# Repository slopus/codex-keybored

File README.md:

<h1 align="center">CODEX KEYBORED</h1>
<h3 align="center">WORK LOAFER EDITION · MECHANICS REV B · ELECTRONICS REV A2</h3>

<p align="center">
  A from-scratch, manufacturable parody of the Codex Micro: Fusion 360 mechanics,<br>
  four quoted CNC parts, a wired six-layer PCB, turnkey assembly instructions, and working USB HID firmware.
</p>

<p align="center">
  <a href="https://happy.engineering/codex-keybored/"><b>VIEW THE MANUFACTURING DOSSIER</b></a>
  &nbsp;·&nbsp;
  <a href="output/CODEX_KEYBORED_RevB_order_handoff.zip"><b>DOWNLOAD COMPLETE HANDOFF</b></a>
  &nbsp;·&nbsp;
  <a href="fusion/Codex_Micro_RevA.f3d"><b>OPEN FUSION ARCHIVE</b></a>
</p>

---

<h1 align="center">THIS IS NOT A DISCLAIMER.<br>THIS IS THE WHOLE POINT.</h1>

<h1 align="center">ABSOLUTELY EVERYTHING HERE IS 100% VIBE-CODED.</h1>

<h1 align="center">
  FROM THE FIRST PROMPT TO FUSION 360, KICAD, GERBERS, FIRMWARE,<br>
  AND A REAL UPLOAD INTO JLCPCB + JLCCNC.
</h1>

<h2 align="center">
  THIS IS THE PRODUCT STORY: ONE CONTINUOUS VIBE<br>
  FROM A PUBLIC PRODUCT IMAGE<br>
  TO A REAL, QUOTED, FACTORY-READY HARDWARE STACK.
</h2>

<p align="center">
  <b>THE DELIGHTFUL PART IS THAT THE VIBE DID NOT STOP WHEN THE WORK BECAME PHYSICAL.</b><br>
  It crossed industrial design, parametric CAD, CNC drawings, multilayer electronics, component sourcing,
  USB firmware, factory testing, pricing, and vendor handoff. Every layer is editable, inspectable, and ready to continue.
</p>

## One vibe, all the way to the factory

Most vibe-coded projects end at a screenshot. This one kept going until the pixels became toleranced solids, the solids became quoted CNC parts, the control layout became a routed six-layer PCB, the PCB became Gerbers/BOM/CPL, the firmware became checksummed factory binaries, and the whole stack became live JLC manufacturing jobs.

That is the fun of this repository: the same conversational build loop moves through every engineering discipline without hiding the seams. “The aluminum base is slightly tilted” became a **5° Fusion body**. “Not a foot, a ring” became a purchased **JIS G‑65 O-ring**, a concentric retention groove, refreshed STEP/DXF/PDF exports, a successful JLCCNC import, a **$68.31** live base quote, and a cleaned cart. “I do not want to solder switches” became a both-side PCBA configuration, consigned-parts manifest, 74-position placement file, manual assembly contract, flashing procedure, and functional acceptance test.

| Vibe-coding pass | What was created | Where it became real |
|---|---|---|
| **Look closely** | Public renders were compared, scaled, and converted into an explicit confirmed/measured/inferred datum set | Research notes + manufacturing dossier |
| **Make it solid** | A parametric 108 × 108 mm assembly, corrected wedge, captured light pipe, joystick cap, and purchased continuous grip ring | Fusion 360 scripts + four STEP/DXF packages + G‑65 vendor reference |
| **Make it electronic** | A clean-room STM32F072 architecture, matrix, USB-C, touch, joystick, 24 RGB pixels, six copper layers | KiCad source + 0-error DRC + IPC netlist |
| **Make it behave** | USB HID firmware, neutral F13–F24 map, RGB safety limit, factory browser test | BIN/HEX/ELF + SHA-256 checksums |
| **Make it buildable** | LCSC mappings, BOM/CPL, specialty-parts sourcing, manual operations, inspection gates | Turnkey factory ZIP + controlled SOP |
| **Make the factory answer** | CAD and fabrication files were uploaded into authenticated quote flows | Four current JLCCNC items + JLCMC G‑65 ring + JLCPCB job Y5 |

```text
PROMPT → RESEARCH → DIMENSIONS → FUSION 360 → STEP/DXF → JLCCNC
                     ↓
              ELECTRICAL PLAN → KICAD → GERBER/BOM/CPL → JLCPCB
                     ↓
              FIRMWARE → FACTORY TEST → TURNKEY HANDOFF → A FEW FINAL SCREWS
```

The result is not “AI made a picture of a keyboard.” The result is a versioned hardware project in which a vibe-driven decision can be traced from sentence to parameter, from parameter to geometry or net, and from production file to a factory price. **That end-to-end continuity is the project.**

---

## The whole device, not just a render

| Mechanical | Electronics | Factory route |
|---|---|---|
| **108 × 108 mm** outer envelope | **90 × 90 mm**, six copper layers | **4 CNC parts** already quoted |
| **5°** machined aluminum wedge | STM32F072 + USB-C + TinyUSB | **5 PCBs / 2 PCBA** in turnkey job Y5 |
| Parametric Fusion assembly + STEP/DXF | 12 keys + encoder + touch + joystick | Specialty parts consigned to the factory |
| Black POM, clear PMMA, 6061-T6, NBR | 24 reverse-mount RGB pixels | Flash, functional test, and evidence in SOP |
| Controlled drawing pack | **0 DRC violations / 0 unconnected nets** | Customer closes only a few enclosure screws |

<table>
  <tr>
    <td width="50%"><br><sub><b>FUSION 360 / TOP</b> — measured mechanical interface</sub></td>
    <td width="50%"><br><sub><b>FUSION 360 / SIDE</b> — corrected 5° wedge</sub></td>
  </tr>
  <tr>
    <td width="50%"><br><sub><b>PCB / TOP</b> — WORK LOAFER EDITION silk</sub></td>
    <td width="50%"><br><sub><b>PCB / BOTTOM</b> — controller island, power, matrix, RGB</sub></td>
  </tr>
</table>

## Yes: the factory does the hand work

> **ZERO SOLDERING AT HOME.** The production route asks JLC to place both-side SMD, manually install the twelve switches and encoder, fit the joystick/FFC, flash the STM32, exercise all 20 USB HID events, inspect all 24 RGB emitters, and install the caps on the primary unit. The customer-facing operation is enclosure closure after first-article approval.

The automatic JLC matcher uses the catalog-only [BOM](electronics/production/codex_micro_wired_revA_jlc_bom.csv) and [CPL](electronics/production/codex_micro_wired_revA_jlc_cpl.csv). The complete manual/secondary-operation contract is in the [turnkey SOP](electronics/production/CODEX_KEYBORED_RevA2_TURNKEY_SOP.md), [expanded BOM](electronics/production/codex_micro_wired_revA_turnkey_bom.csv), [74-position CPL](electronics/production/codex_micro_wired_revA_turnkey_cpl.csv), and [consigned-parts manifest](electronics/production/codex_micro_wired_revA_consigned_parts.csv).

```text
SOURCE SPECIALTY PARTS  →  BOTH-SIDE PCBA  →  MANUAL CONTROLS
         →  FLASH + FUNCTION TEST  →  PHOTO EVIDENCE  →  ENCLOSURE CLOSURE
```

## Live manufacturing snapshot

Quotes were captured in an authenticated JLC session on **July 17, 2026**. Prices are dynamic and exclude possible tax, duty, and engineering-review additions.

| Job | Configuration | Captured price |
|---|---|---:|
| CM2-001 upper housing | CNC polished black POM, qty 1 | **$88.97** |
| CM2-002 angled weight | CNC 6061-T6, 5° wedge + G‑65 groove, qty 1 | **$68.31** |
| CM2-003 light pipe | CNC clear cast PMMA, polished edges + frosted face, qty 1 | **$45.70** |
| CM2-004 joystick cap | CNC POM fit prototype, qty 1 | **$19.42** |
| CM2-005 continuous grip ring | JLCMC AMFG-P5-A65-65 / black NBR 65A, qty 1 | **$0.16** |
| **Mechanical subtotal** | Four current CNC parts + purchased ring | **$222.56** |
| **JLCPCB turnkey base** | Five PCBs + two both-side Standard PCBA | **$193.01** |
| **Captured manufacturing floor** | Mechanical merchandise + PCBA base, before manual review, special parts, tax/duty/shipping | **$415.57** |

The **$193.01** PCB/PCBA figure is a captured base, not a promise of a finished-device total. Programming, functional test, secondary manual operations, and consigned-part handling remain quote-after-review. The saved cart proves that the geometry and six-layer board can enter the vendor workflow; JLC engineering approval is still the gate before payment.

## What is actually in the repository

| Area | Source of truth | Ready-to-send artifact |
|---|---|---|
| Fusion mechanics | [`fusion/build_codex_micro_mechanical.py`](fusion/build_codex_micro_mechanical.py) | [`Codex_Micro_RevA.f3d`](fusion/Codex_Micro_RevA.f3d) |
| CNC geometry | Fusion BRep bodies | [`cnc/STEP/`](cnc/STEP/) + [`cnc/DXF/`](cnc/DXF/) |
| CNC dimensions | Parametric model + controlled notes | [`CM2_CNC_Drawing_Pack_RevB.pdf`](cnc/drawings/CM2_CNC_Drawing_Pack_RevB.pdf) |
| PCB connectivity/layout | [`codex_micro_wired_revA.kicad_pcb`](electronics/kicad/codex_micro_wired_revA.kicad_pcb) | [Gerber/drill ZIP](electronics/production/codex_micro_wired_revA_gerbers.zip) |
| Assembly data | Board-derived generator | [JLC BOM](electronics/production/codex_micro_wired_revA_jlc_bom.csv) + [JLC CPL](electronics/production/codex_micro_wired_revA_jlc_cpl.csv) |
| Principle schematic | Final routed connectivity | [Three-sheet PDF](output/pdf/CODEX_KEYBORED_RevA2_schematic.pdf) + [IPC-D-356](electronics/production/netlist/CODEX_KEYBORED_RevA2.ipc) |
| Firmware | [`firmware/stm32/`](firmware/stm32/) | [BIN](firmware/stm32/release/codeks_keybored_revA.bin) + [HEX](firmware/stm32/release/codeks_keybored_revA.hex) + [checksums](firmware/stm32/release/SHA256SUMS.txt) |
| Factory contract | Mechanics Rev B + electronics Rev A2 | [Complete order handoff ZIP](output/CODEX_KEYBORED_RevB_order_handoff.zip) + [mechanical factory ZIP](output/CODEX_KEYBORED_RevB_mechanical_factory_handoff.zip) |
| Full report | Evidence, screenshots, prices, sources | [Single-page dossier](https://happy.engineering/codex-keybored/) + [Rev B PDF](output/pdf/CODEX-KEYBORED-Manufacturing-Dossier-RevB.pdf) |

## Electrical architecture

- STM32F072CBT6, 128 KB flash, crystal-less HSI48 + CRS USB.
- USB-C device input, dual 5.1 kΩ CC resistors, USBLC6 ESD protection.
- Six layers: `F.Cu`, GND plane, two signal layers, `+5V` plane, `B.Cu`.
- Twelve low-profile matrix switches plus clickable encoder.
- Capacitive touch and two-channel analog planar joystick.
- 24 × SK6812MINI-E: twelve per-key, nine underglow, three status.
- Build-verified TinyUSB firmware with BIN/HEX/ELF artifacts and a browser factory test.
- Housing interface intentionally remains compatible with a future replacement ESP32-S3/BLE board.

## Mechanical datum set

The coordinate origin is the device center. `+Y` points toward the rear edge; `+Z` points upward.

| Parameter | Value | Confidence | Basis |
|---|---:|---|---|
| Key pitch | 19.05 mm | **CONFIRMED** | Work Louder MX keycap specification |
| Installed keyboard switches | 12 | **CONFIRMED** | Visible layout + Creator Micro 2 specification |
| Total mechanical switch inputs | 13 | **CONFIRMED** | Includes encoder push |
| Outer envelope | 108 × 108 mm | **MEASURED** | Official top render scaled from key centers |
| Top PCB/panel | 90 × 90 × 1.6 mm | **MEASURED / INFERRED** | Render scale + standard PCB thickness |
| PCB screw pitch | 78 × 78 mm | **MEASURED** | Provisional ±0.5 mm |
| Upper housing | 108 × 108 × 10.3 mm, R14 | **MEASURED** | Public front/side/top renders |
| Aluminum bottom | Ø94 mm, 3.8→12.0 mm, 5° | **MEASURED / INFERRED** | Side profile + CNC construction |
| G‑65 retention groove | Ø67.5 mm centerline × 3.6 W × 2.2 D | **ENGINEERED** | G‑65 section, screw clearance, 1.6 mm minimum Al floor |
| Continuous grip ring | JIS B 2401 G‑65, ID 64.4, section 3.1, OD 70.6 mm | **PURCHASED / VERIFIED** | JLCMC AMFG-P5-A65-65 |
| Joystick candidate | Alps RKJXY1000006 | **CANDIDATE** | Available electrical/mechanical sibling |

Confidence language is deliberate:

- **CONFIRMED** — explicitly published by OpenAI, Work Louder, or a component manufacturer.
- **MEASURED** — scaled from a public, near-orthographic product render.
- **INFERRED** — a manufacturable placeholder that still requires physical first-article inspection.
- **ENGINEERED** — a derived interface sized from known parts, tolerances, and adjacent clearances.
- **PURCHASED / VERIFIED** — an exact orderable catalog part with checked dimensions and a live cart entry.

## CNC material directions

The current quoted Rev B build uses polished black POM for the upper housing and joystick cap, black-anodized 6061-T6 for the 5° base, clear cast PMMA for the captured light pipe, and a purchased black NBR G‑65 ring. A wood upper remains a future material experiment, but it is not the current cart configuration.

All four STEP files passed JLC's automated CNC import. The current bottom was explicitly corrected from an early flat disc to the observed **5° wedge**, then revised again with the G‑65 retention groove before the **$68.31** configuration was saved. Obsolete flat/no-groove parts and individual rubber feet were removed from the cart.

## Reproduce it

1. Open or create the Fusion document named `Codex`, then run [`fusion/build_codex_micro_mechanical.py`](fusion/build_codex_micro_mechanical.py).
2. Export/audit CNC bodies with the scripts in [`fusion/`](fusion/) and compare them with the controlled drawing pack.
3. Open the board in KiCad 10 and verify the committed DRC report before regenerating fabrication data.
4. Build the STM32 target from [`firmware/stm32/`](firmware/stm32/) or use the checksummed release image.
5. Upload the Gerber ZIP, JLC BOM/CPL, CNC STEP files, drawing pack, and turnkey factory ZIP.
6. Do not authorize production until JLC DFM, polarity/rotation, manual-operation scope, and first-article dimensions are reviewed.

## Prototype status and provenance

This is an **independent private prototype**, reconstructed from official public product renders and published platform/component documentation. It is not an official OpenAI or Work Louder CAD/electronics release, is not affiliated with or endorsed by either company, and contains no leaked manufacturing data.

The digital production gate is clean: Gerbers, drill files, BOM/CPL, IPC netlist, three-sheet principle schematic, firmware, STEP/DXF, drawings, and vendor quote evidence are present. The physical gate is still open: no fabricated Rev A2 board has completed electrical bring-up, EMC evaluation, or dimensional fit-check. Use a current-limited supply, verify the 3.3 V rail and SWD first, and treat the first order as an engineering prototype.

Primary research links and detailed source notes live in the [manufacturing dossier](https://happy.engineering/codex-keybored/) and [`firmware-and-compliance-notes.md`](firmware-and-compliance-notes.md).

---

<h2 align="center">PRESS KEYS. SHIP BUGS.</h2>
<p align="center"><b>CODEX KEYBORED / WORK LOAFER EDITION / MECHANICS REV B + ELECTRONICS REV A2</b></p>

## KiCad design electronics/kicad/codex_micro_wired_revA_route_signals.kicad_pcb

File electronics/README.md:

# CODEX KEYBORED Wired Rev A2 — production notes

This directory contains a mechanically compatible **wired prototype**, not a
reverse-engineered copy of the unpublished Work Louder electronics.  The board
uses a clean-room STM32F072/USB-C design and keeps the 90 × 90 mm top-panel outline
so a later ESP32-S3/BLE controller can replace it without changing the housing.

## Electrical architecture

- Six copper layers: `F.Cu`, ground plane, two signal layers, `+5V` plane,
  `B.Cu`.
- STM32F072CBT6 with 128 KB internal flash, HSI48 + CRS crystal-less USB, and
  ME6211 3.3 V LDO. No external flash or crystal is required.
- USB-C device input with two 5.1 kΩ CC resistors and USBLC6 ESD protection.
  The reversible connector pairs cross on `SIGNAL_1` / `SIGNAL_2` before PA11/PA12.
- Twelve Gateron KS-33 / wrk. LP1-family matrix switches plus encoder push.
- Clickable encoder, TTP223-class touch input and two-channel analog joystick.
- 24 SK6812MINI-E pixels through a 5 V-compatible AHCT buffer: 12 per-key,
  nine perimeter underglow and three status LEDs.
- NRST, BOOT0 and SWD bring-up access.

The PCB is generated from `generate_wired_reva.py`; it deliberately does not
depend on a GUI schematic editor. Pad/net assignments in the generated KiCad
board are the electrical source of truth. `generate_jlc_outputs.py` derives the
assembly files from that same board and fails if an unmapped fitted reference is
encountered.

Final automated checks report **0 DRC violations and 0 unconnected nets**.
`docs/schematic.html` is a three-sheet engineering principle schematic derived
from that final connectivity; the IPC-D-356 file is the machine-readable netlist.

## Production files

- `production/codex_micro_wired_revA_gerbers.zip` — JLCPCB fabrication upload.
- `production/codex_micro_wired_revA_jlc_bom.csv` — JLCPCB BOM with LCSC IDs.
- `production/codex_micro_wired_revA_jlc_cpl.csv` — machine placement file.
- `production/codex_micro_wired_revA_turnkey_bom.csv` — both-side BOM including
  consigned/manual controls and factory-programming buttons.
- `production/codex_micro_wired_revA_turnkey_cpl.csv` — all 74 machine and
  manual placement centers.
- `production/codex_micro_wired_revA_consigned_parts.csv` — direct-to-JLC
  sourcing quantities for WRK-LP1, joystick, keycaps, and dial cap.
- `production/CODEX_KEYBORED_RevA2_TURNKEY_SOP.md` — assembly, programming,
  functional test, evidence, and delivery acceptance instructions.
- `production/codex_micro_wired_revA_hand_assembly.csv` — legacy list of parts
  omitted by the saved bottom-only baseline quote.
- `production/codex_micro_wired_revA_drc.json` — final clean DRC report.
- `production/netlist/CODEX_KEYBORED_RevA2.ipc` — IPC-D-356 connectivity.
- `production/schematic/CODEX_KEYBORED_RevA2_schematic.pdf` — principle schematic.

JLC cart job Y5 / `SMT026071763199-3086316A` is Standard PCBA on **both sides**:
five PCBs and two assembled boards. Its automatic matcher uses the catalog-only
`*_jlc_bom.csv` and `*_jlc_cpl.csv` and confirmed all 16 groups. The expanded
`turnkey` BOM/CPL and consigned-parts CSV are factory engineering references for
manual installation of `SW1–SW12`, the encoder, and the joystick/FFC. The
captured base is $193.01; programming, FCT, and manual engineering remain
quote-after-review. These are contract-assembly operations—not customer work.
Review every polarity/rotation and obtain JLC engineering approval before
confirming a paid order.

## Bring-up gate

This is a prototype design and has not been electrically tested on fabricated
hardware. Before attaching a computer, use a current-limited 5 V supply and
verify the 3.3 V rail, inspect for shorts, confirm SWD/NRST, and only then
enumerate USB. The supplied firmware limits
RGB channels to 4/255; still populate the chain last, or depopulate its bulk
capacitor/level shifter for the earliest rail-only bring-up.

The selected LCSC mappings and exact quantities are listed in the BOM. Part
stock and JLCPCB assembly classification can change; a successful web quote is
not an engineering substitute for the vendor's final DFM and placement review.

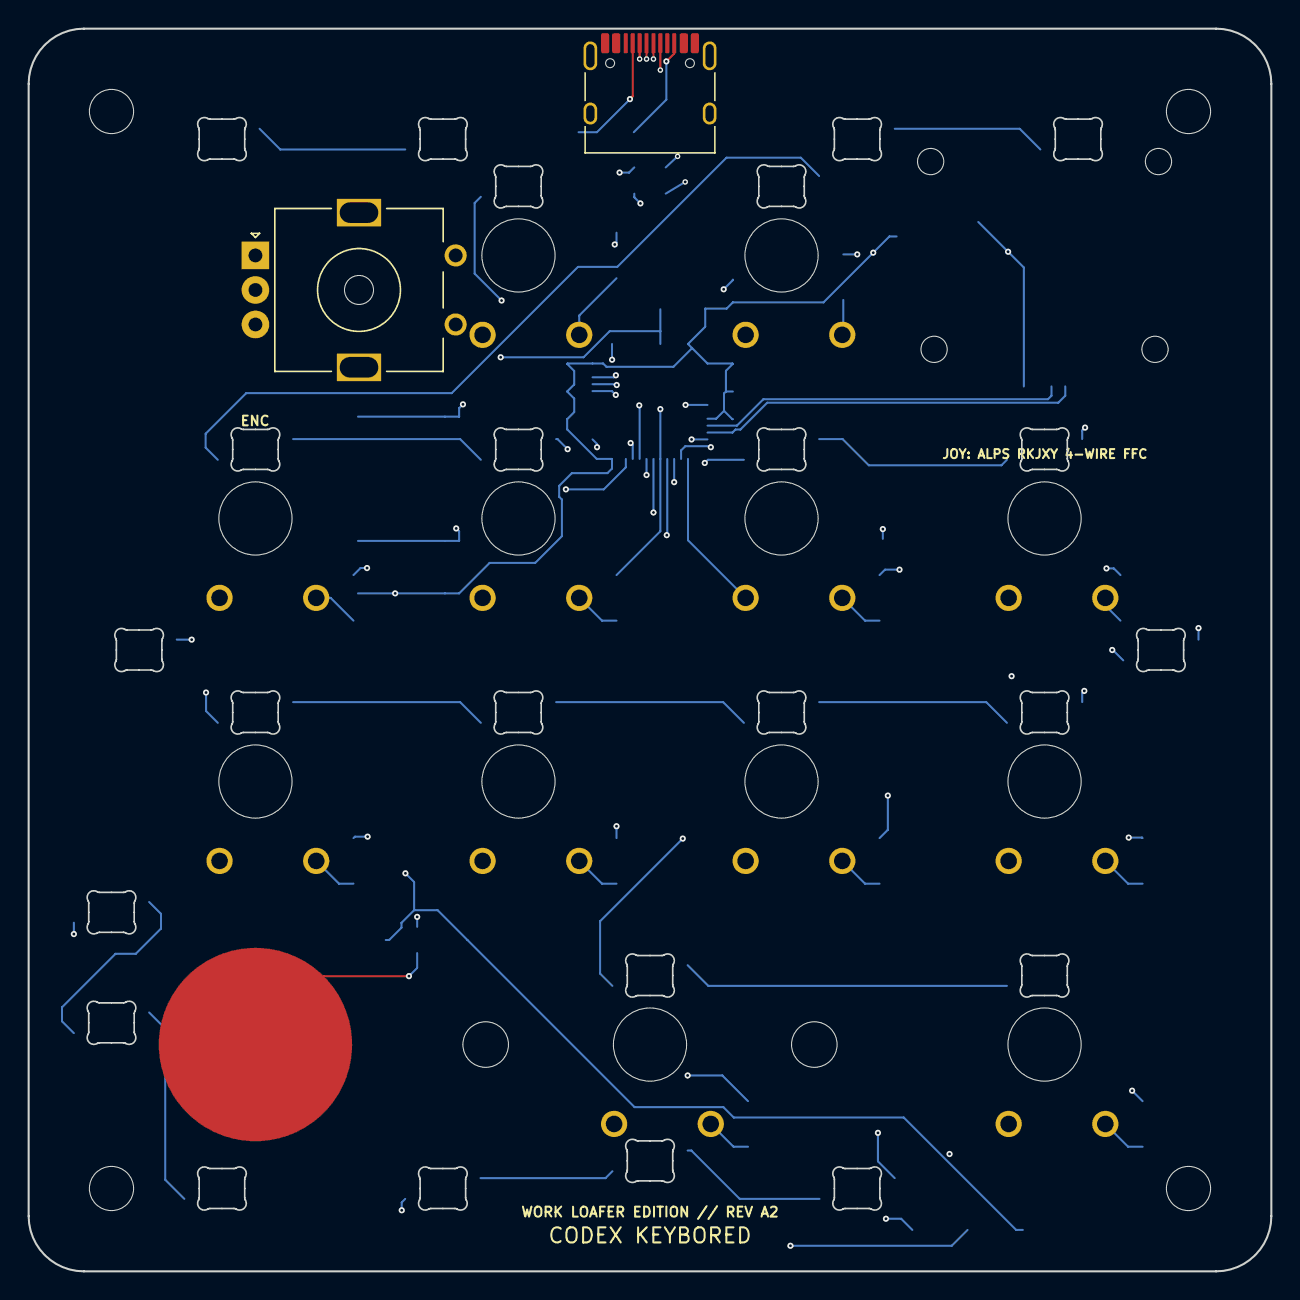
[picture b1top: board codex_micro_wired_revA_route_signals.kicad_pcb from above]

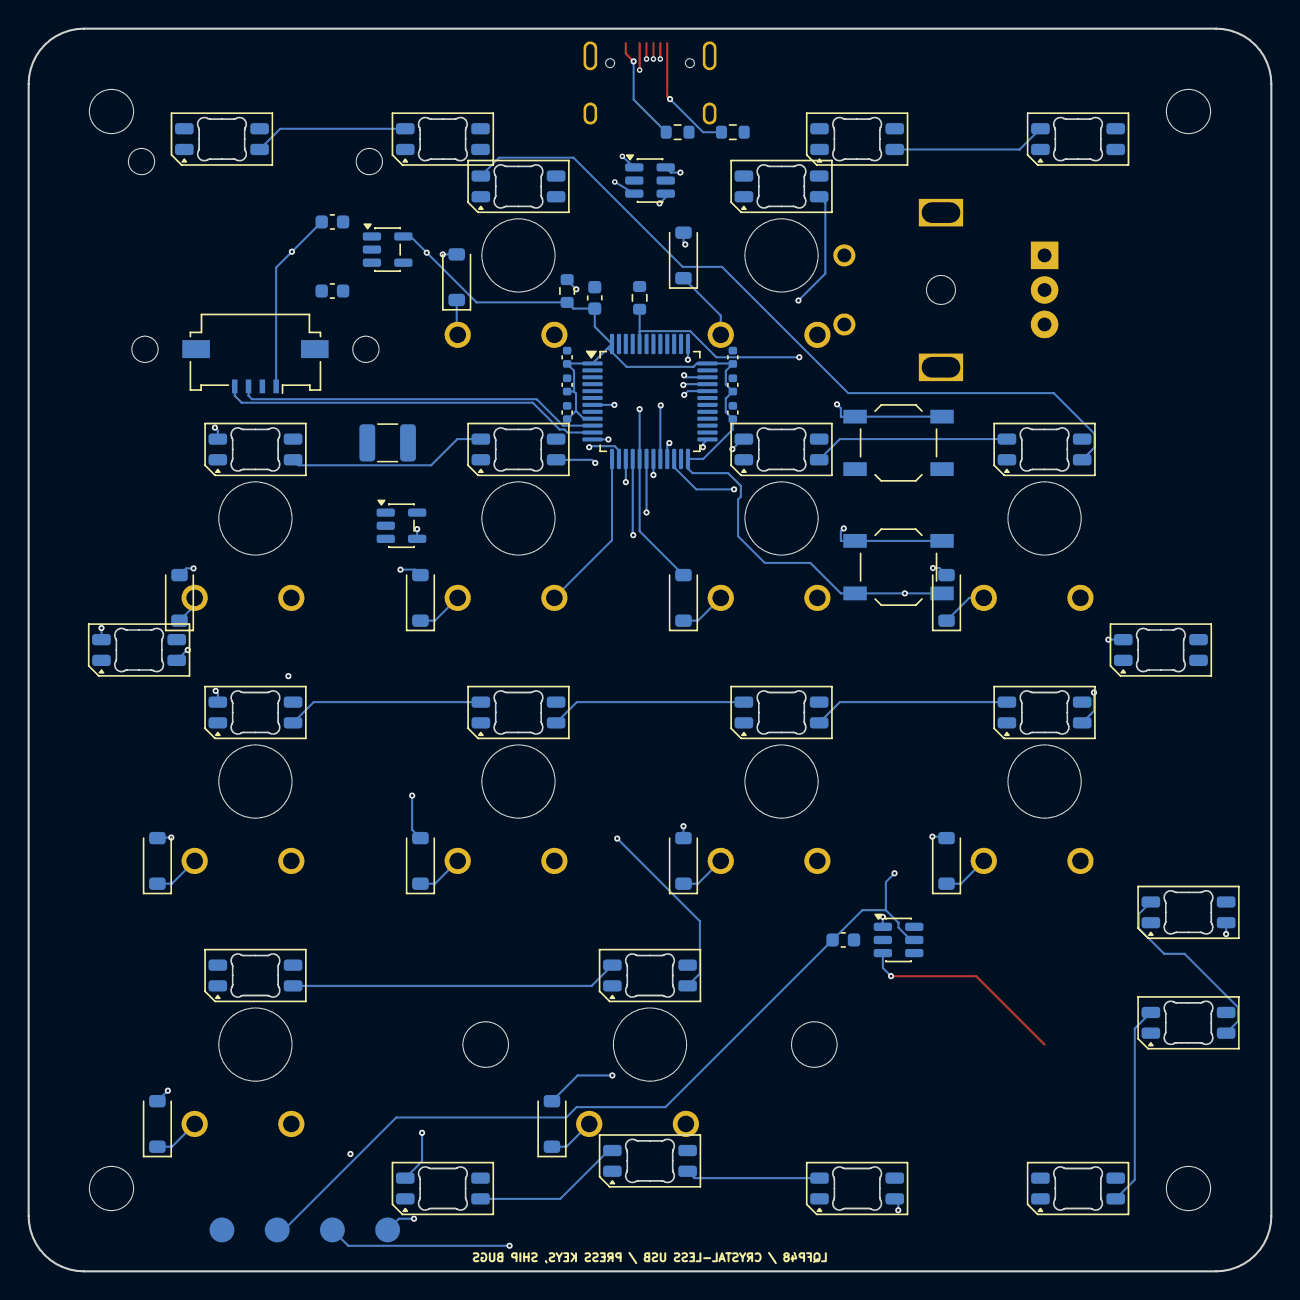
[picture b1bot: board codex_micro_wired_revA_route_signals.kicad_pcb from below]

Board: 6 copper layers, 90.0 x 90.0 mm, 85 parts (59 on the bottom side), 64 nets.

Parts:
C1, C2: 10uF; C_0603_1608Metric
C3, C4, C5, C6, C7: 100nF_3V3; C_0402_1005Metric
C8: 1uF_VDDA; C_0402_1005Metric
C9: 4.7uF_3V3_BULK; C_0603_1608Metric
C10: 100nF_TOUCH; C_0603_1608Metric
C19: CL32A107MQVNNNE_100uF_6V3; C_1210_3225Metric
D1, D2, D3, D4, D5, D6, D7, D8, D9, D10, D11, D12: 1N4148W; D_SOD-123
E1: CAP_TOUCH_14MM
ENC1: EC11E_VERTICAL_CLICK; RotaryEncoder_Alps_EC11E-Switch_Vertical_H20mm_MountingHoles
H1, H2, H3, H4: MountingHole_M3
HSTAB1, HSTAB2: MountingHole_M3
J1: USB_C_HRO_TYPE-C-31-M-12; USB_C_Receptacle_HRO_TYPE-C-31-M-12
J2: RKJXY_4WIRE_FFC; Molex_200528-0040_1x04-1MP_P1.00mm_Horizontal
JOY1: Alps_RKJXY100000A_MECHANICAL
LED1, LED2, LED3, LED4, LED5, LED6, LED7, LED8, LED9, LED10, LED11, LED12, LED13, LED14, LED15, LED16, LED17, LED18, LED19, LED20, LED21, LED22, LED23, LED24: SK6812MINI-E; LED_SK6812MINI-E_3.2x2.8mm_P1.5mm_ReverseMount
R1: 5.1k_CC1; R_0603_1608Metric
R2: 5.1k_CC2; R_0603_1608Metric
R3: 10k_NRST_PULLUP; R_0603_1608Metric
R4: 10k_BOOT0_PULLDOWN; R_0603_1608Metric
SW1, SW2, SW3, SW4, SW5, SW6, SW7, SW8, SW9, SW10, SW11, SW12: Gateron_KS-33_H10B050NN-Y24
SW13: RESET; SW_SPST_TL3342
SW14: BOOT; SW_SPST_TL3342
TP1: SWCLK
TP2: SWD
TP3: 3V3
TP4: GND
U1: STM32F072CBT6; LQFP-48_7x7mm_P0.5mm
U3: ME6211C33M5G; SOT-23-5
U4: USBLC6-2SC6; SOT-23-6
U5: SN74AHCT1G125DBVR; SOT-23-5
U6: TTP223-BA6-TD; SOT-23-6

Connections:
+3V3: C1.1, C3.1, C4.1, C5.1, C6.1, C7.1, C8.1, C9.1, C10.1, J2.1, R3.1, SW14.2, TP3.1, U1.1, U1.9, U1.24, U1.36, U1.48, U3.5, U6.5
+5V: C2.1, C19.1, J1.A4, J1.A9, J1.B4, J1.B9, LED1.1, LED2.1, LED3.1, LED4.1, LED5.1, LED6.1, LED7.1, LED8.1, LED9.1, LED10.1, LED11.1, LED12.1, LED13.1, LED14.1, LED15.1, LED16.1, LED17.1, LED18.1, LED19.1, LED20.1, LED21.1, LED22.1, LED23.1, LED24.1, U3.1, U3.3, U4.5, U5.5
BOOT0: R4.1, SW14.1, U1.44
COL0: D3.2, D7.2, U1.16
COL1: D1.2, D4.2, D8.2, D11.2, U1.17
COL2: D2.2, D5.2, D9.2, U1.18
COL3: D6.2, D10.2, D12.2, U1.19
ENC_A: ENC1.A, U1.20
ENC_B: ENC1.B, U1.21
ENC_SW: ENC1.S1, U1.22
JOY_X: J2.3, U1.10
JOY_Y: J2.4, U1.11
LED_D1: LED1.2, LED2.4
LED_D2: LED2.2, LED3.4
LED_D3: LED3.2, LED4.4
LED_D4: LED4.2, LED5.4
LED_D5: LED5.2, LED6.4
LED_D6: LED6.2, LED7.4
LED_D7: LED7.2, LED8.4
LED_D8: LED8.2, LED9.4
LED_D9: LED9.2, LED10.4
LED_D10: LED10.2, LED11.4
LED_D11: LED11.2, LED12.4
LED_D12: LED12.2, LED13.4
LED_D13: LED13.2, LED14.4
LED_D14: LED14.2, LED15.4
LED_D15: LED15.2, LED16.4
LED_D16: LED16.2, LED17.4
LED_D17: LED17.2, LED18.4
LED_D18: LED18.2, LED19.4
LED_D19: LED19.2, LED20.4
LED_D20: LED20.2, LED21.4
LED_D21: LED21.2, LED22.4
LED_D22: LED22.2, LED23.4
LED_D23: LED23.2, LED24.4
NRST: R3.2, SW13.1, U1.7
RGB_3V3: U1.26, U5.2
RGB_5V: LED1.4, U5.4
ROW0: SW1.1, SW2.1, U1.12
ROW1: SW3.1, SW4.1, SW5.1, SW6.1, U1.13
ROW2: SW7.1, SW8.1, SW9.1, SW10.1, U1.14
ROW3: SW11.1, SW12.1, U1.15
SW1_D: D1.1, SW1.2
SW2_D: D2.1, SW2.2
SW3_D: D3.1, SW3.2
SW4_D: D4.1, SW4.2
SW5_D: D5.1, SW5.2
SW6_D: D6.1, SW6.2
SW7_D: D7.1, SW7.2
SW8_D: D8.1, SW8.2
SW9_D: D9.1, SW9.2
SW10_D: D10.1, SW10.2
SW11_D: D11.1, SW11.2
SW12_D: D12.1, SW12.2
SWCLK: TP1.1, U1.37
SWD: TP2.1, U1.34
TOUCH: U1.25, U6.1
TOUCH_ELECTRODE: E1.1, U6.3
USB_CC1: J1.A5, R1.1
USB_CC2: J1.B5, R2.1
USB_DM_CONN: J1.A7, J1.B7, U4.3
USB_DM_PROT: U1.32, U4.4
USB_DP_CONN: J1.A6, J1.B6, U4.1
USB_DP_PROT: U1.33, U4.6

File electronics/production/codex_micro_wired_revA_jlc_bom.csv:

Comment,Designator,Footprint,LCSC Part #,Manufacturer Part #
10uF 10V X5R 0603,"C1,C2",C_0603_1608Metric,C19702,CL10A106KP8NNNC
100nF 16V X7R 0402,"C3,C4,C5,C6,C7",C_0402_1005Metric,C1525,CL05B104KO5NNNC
1uF 10V X5R 0402,C8,C_0402_1005Metric,C52923,CL05A105KP5NNNC
4.7uF 10V X5R 0603,C9,C_0603_1608Metric,C19666,CL10A475KO8NNNC
100nF 50V X7R 0603,C10,C_0603_1608Metric,C14663,CC0603KRX7R9BB104
CL32A107MQVNNNE 100uF 6.3V,C19,C_1210_3225Metric,C49066,CL32A107MQVNNNE
1N4148W,"D1,D2,D3,D4,D5,D6,D7,D8,D9,D10,D11,D12",D_SOD-123,C81598,1N4148W
TYPE-C-31-M-12,J1,USB_C_Receptacle_HRO_TYPE-C-31-M-12,C165948,TYPE-C-31-M-12
SK6812MINI-E,"LED1,LED2,LED3,LED4,LED5,LED6,LED7,LED8,LED9,LED10,LED11,LED12,LED13,LED14,LED15,LED16,LED17,LED18,LED19,LED20,LED21,LED22,LED23,LED24",LED_SK6812MINI-E_3.2x2.8mm_P1.5mm_ReverseMount,C5149201,SK6812MINI-E
5.1k 1% 0603,"R1,R2",R_0603_1608Metric,C23186,0603WAF5101T5E
10k 1% 0603,"R3,R4",R_0603_1608Metric,C98220,RC0603FR-0710KL
STM32F072CBT6 128KB crystal-less USB,U1,LQFP-48_7x7mm_P0.5mm,C81720,STM32F072CBT6
ME6211C33M5G-N,U3,SOT-23-5,C82942,ME6211C33M5G-N
USBLC6-2SC6,U4,SOT-23-6,C7519,USBLC6-2SC6
SN74AHCT1G125DBVR,U5,SOT-23-5,C7484,SN74AHCT1G125DBVR
TTP223-BA6-TD,U6,SOT-23-6,C42422127,TTP223-BA6-TD

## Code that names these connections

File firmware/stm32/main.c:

#include <stdbool.h>
#include <stdint.h>
#include <string.h>

#include "bsp/board_api.h"
#include "stm32f0xx_hal.h"
#include "stm32f0xx_hal_adc.h"
#include "stm32f0xx_hal_adc_ex.h"
#include "tusb.h"

typedef struct { GPIO_TypeDef *port; uint16_t pin; } gpio_t;

static gpio_t const rows[4] = {
  {GPIOA, GPIO_PIN_2}, {GPIOA, GPIO_PIN_3},
  {GPIOA, GPIO_PIN_4}, {GPIOA, GPIO_PIN_5},
};
static gpio_t const cols[4] = {
  {GPIOA, GPIO_PIN_6}, {GPIOA, GPIO_PIN_7},
  {GPIOB, GPIO_PIN_0}, {GPIOB, GPIO_PIN_1},
};
static gpio_t const enc_a = {GPIOB, GPIO_PIN_2};
static gpio_t const enc_b = {GPIOB, GPIO_PIN_10};
static gpio_t const enc_sw = {GPIOB, GPIO_PIN_11};
static gpio_t const touch = {GPIOB, GPIO_PIN_12};
#define RGB_PORT GPIOB
#define RGB_PIN GPIO_PIN_13
#define RGB_COUNT 24

static uint8_t const keymap[4][4] = {
  {0, HID_KEY_F13, HID_KEY_F14, 0},
  {HID_KEY_F15, HID_KEY_F16, HID_KEY_F17, HID_KEY_F18},
  {HID_KEY_F19, HID_KEY_F20, HID_KEY_F21, HID_KEY_F22},
  {0, HID_KEY_F23, 0, HID_KEY_F24},
};
static uint8_t stable[4][4];
static uint8_t integrator[4][4];
static uint8_t encoder_last;
static int8_t encoder_delta;
static ADC_HandleTypeDef hadc;

static void configure_pin(gpio_t gpio, uint32_t mode, uint32_t pull) {
  GPIO_InitTypeDef init = {0};
  init.Pin = gpio.pin;
  init.Mode = mode;
  init.Pull = pull;
  init.Speed = GPIO_SPEED_FREQ_HIGH;
  HAL_GPIO_Init(gpio.port, &init);
}

static void keyboard_io_init(void) {
  for (unsigned i = 0; i < 4; i++) configure_pin(rows[i], GPIO_MODE_INPUT, GPIO_NOPULL);
  for (unsigned i = 0; i < 4; i++) configure_pin(cols[i], GPIO_MODE_INPUT, GPIO_PULLUP);
  configure_pin(enc_a, GPIO_MODE_INPUT, GPIO_PULLUP);
  configure_pin(enc_b, GPIO_MODE_INPUT, GPIO_PULLUP);
  configure_pin(enc_sw, GPIO_MODE_INPUT, GPIO_PULLUP);
  configure_pin(touch, GPIO_MODE_INPUT, GPIO_PULLDOWN);
  configure_pin((gpio_t){RGB_PORT, RGB_PIN}, GPIO_MODE_OUTPUT_PP, GPIO_NOPULL);
  HAL_GPIO_WritePin(RGB_PORT, RGB_PIN, GPIO_PIN_RESET);
  encoder_last = (HAL_GPIO_ReadPin(enc_a.port, enc_a.pin) << 1) |
                 HAL_GPIO_ReadPin(enc_b.port, enc_b.pin);
}

static void adc_init_local(void) {
  GPIO_InitTypeDef analog = {0};
  analog.Pin = GPIO_PIN_0 | GPIO_PIN_1;
  analog.Mode = GPIO_MODE_ANALOG;
  analog.Pull = GPIO_NOPULL;
  HAL_GPIO_Init(GPIOA, &analog);
  __HAL_RCC_ADC1_CLK_ENABLE();
  hadc.Instance = ADC1;
  hadc.Init.ClockPrescaler = ADC_CLOCK_ASYNC_DIV1;
  hadc.Init.Resolution = ADC_RESOLUTION_12B;
  hadc.Init.DataAlign = ADC_DATAALIGN_RIGHT;
  hadc.Init.ScanConvMode = ADC_SCAN_DIRECTION_FORWARD;
  hadc.Init.EOCSelection = ADC_EOC_SINGLE_CONV;
  hadc.Init.LowPowerAutoWait = DISABLE;
  hadc.Init.LowPowerAutoPowerOff = DISABLE;
  hadc.Init.ContinuousConvMode = DISABLE;
  hadc.Init.DiscontinuousConvMode = DISABLE;
  hadc.Init.ExternalTrigConv = ADC_SOFTWARE_START;
  hadc.Init.ExternalTrigConvEdge = ADC_EXTERNALTRIGCONVEDGE_NONE;
  hadc.Init.DMAContinuousRequests = DISABLE;
  hadc.Init.Overrun = ADC_OVR_DATA_PRESERVED;
  HAL_ADC_Init(&hadc);
  HAL_ADCEx_Calibration_Start(&hadc);
}

static uint16_t adc_read_channel(uint32_t channel) {
  ADC_ChannelConfTypeDef config = {0};
  config.Channel = channel;
  config.Rank = ADC_RANK_CHANNEL_NUMBER;
  config.SamplingTime = ADC_SAMPLETIME_41CYCLES_5;
  HAL_ADC_ConfigChannel(&hadc, &config);
  HAL_ADC_Start(&hadc);
  HAL_ADC_PollForConversion(&hadc, 2);
  uint16_t result = (uint16_t)HAL_ADC_GetValue(&hadc);
  HAL_ADC_Stop(&hadc);
  return result;
}

static void scan_matrix(void) {
  for (unsigned row = 0; row < 4; row++) {
    configure_pin(rows[row], GPIO_MODE_OUTPUT_PP, GPIO_NOPULL);
    HAL_GPIO_WritePin(rows[row].port, rows[row].pin, GPIO_PIN_RESET);
    for (volatile unsigned delay = 0; delay < 40; delay++) __NOP();
    for (unsigned col = 0; col < 4; col++) {
      bool pressed = HAL_GPIO_ReadPin(cols[col].port, cols[col].pin) == GPIO_PIN_RESET;
      uint8_t *acc = &integrator[row][col];
      if (pressed && *acc < 5) (*acc)++;
      if (!pressed && *acc > 0) (*acc)--;
      if (*acc == 5) stable[row][col] = 1;
      if (*acc == 0) stable[row][col] = 0;
    }
    configure_pin(rows[row], GPIO_MODE_INPUT, GPIO_NOPULL);
  }
}

static void encoder_update(void) {
  uint8_t now = (HAL_GPIO_ReadPin(enc_a.port, enc_a.pin) << 1) |
                HAL_GPIO_ReadPin(enc_b.port, enc_b.pin);
  static int8_t const table[16] = {
    0, -1, 1, 0, 1, 0, 0, -1, -1, 0, 0, 1, 0, 1, -1, 0
  };
  encoder_delta += table[(encoder_last << 2) | now];
  encoder_last = now;
}

static inline void rgb_delay(unsigned count) {
  while (count--) __NOP();
}

static void rgb_bit(bool one) {
  RGB_PORT->BSRR = RGB_PIN;
  rgb_delay(one ? 17 : 6);
  RGB_PORT->BRR = RGB_PIN;
  rgb_delay(one ? 7 : 18);
}

static void rgb_word(uint32_t grb) {
  for (int bit = 23; bit >= 0; bit--) rgb_bit((grb >> bit) & 1u);
}

static uint32_t grb(uint8_t red, uint8_t green, uint8_t blue) {
  return ((uint32_t)green << 16) | ((uint32_t)red << 8) | blue;
}

static bool key_led_pressed(uint8_t index) {
  static uint8_t const positions[12][2] = {
    {0,1}, {0,2}, {1,0}, {1,1}, {1,2}, {1,3},
    {2,0}, {2,1}, {2,2}, {2,3}, {3,1}, {3,3},
  };
  return stable[positions[index][0]][positions[index][1]];
}

static void send_rgb_frame(void) {
  __disable_irq();
  for (uint8_t i = 0; i < RGB_COUNT; i++) {
    uint32_t color;
    if (i < 12) color = key_led_pressed(i) ? grb(4,1,0) : (i < 6 ? grb(1,4,0) : grb(2,2,2));
    else if (i < 21) color = grb(1,3,0);
    else color = grb(0,1,4);
    rgb_word(color);
  }
  __enable_irq();
  HAL_Delay(1);
}

static void add_key(uint8_t key, uint8_t keys[6], uint8_t *count) {
  if (key && *count < 6) keys[(*count)++] = key;
}

static void send_report(void) {
  if (!tud_hid_ready()) return;
  uint8_t keys[6] = {0};
  uint8_t count = 0;
  for (unsigned row = 0; row < 4; row++)
    for (unsigned col = 0; col < 4; col++)
      if (stable[row][col]) add_key(keymap[row][col], keys, &count);
  if (HAL_GPIO_ReadPin(enc_sw.port, enc_sw.pin) == GPIO_PIN_RESET)
    add_key(HID_KEY_KEYPAD_ENTER, keys, &count);
  if (HAL_GPIO_ReadPin(touch.port, touch.pin) == GPIO_PIN_SET)
    add_key(HID_KEY_F12, keys, &count);

  uint16_t x = adc_read_channel(ADC_CHANNEL_0);
  uint16_t y = adc_read_channel(ADC_CHANNEL_1);
  if (x < 900) add_key(HID_KEY_ARROW_LEFT, keys, &count);
  if (x > 3200) add_key(HID_KEY_ARROW_RIGHT, keys, &count);
  if (y < 900) add_key(HID_KEY_ARROW_DOWN, keys, &count);
  if (y > 3200) add_key(HID_KEY_ARROW_UP, keys, &count);
  if (encoder_delta >= 4) { add_key(HID_KEY_PAGE_UP, keys, &count); encoder_delta = 0; }
  if (encoder_delta <= -4) { add_key(HID_KEY_PAGE_DOWN, keys, &count); encoder_delta = 0; }
  tud_hid_keyboard_report(0, 0, keys);
}

int main(void) {
  board_init();
  keyboard_io_init();
  adc_init_local();
  tusb_rhport_init_t dev = {.role = TUSB_ROLE_DEVICE, .speed = TUSB_SPEED_FULL};
  tusb_init(BOARD_TUD_RHPORT, &dev);
  board_init_after_tusb();

  uint32_t next_scan = 0;
  uint32_t next_rgb = 0;
  while (1) {
    tud_task();
    uint32_t now = HAL_GetTick();
    if ((int32_t)(now - next_scan) >= 0) {
      next_scan = now + 1;
      scan_matrix();
      encoder_update();
      send_report();
    }
    if ((int32_t)(now - next_rgb) >= 0) {
      next_rgb = now + 20;
      send_rgb_frame();
    }
  }
}
